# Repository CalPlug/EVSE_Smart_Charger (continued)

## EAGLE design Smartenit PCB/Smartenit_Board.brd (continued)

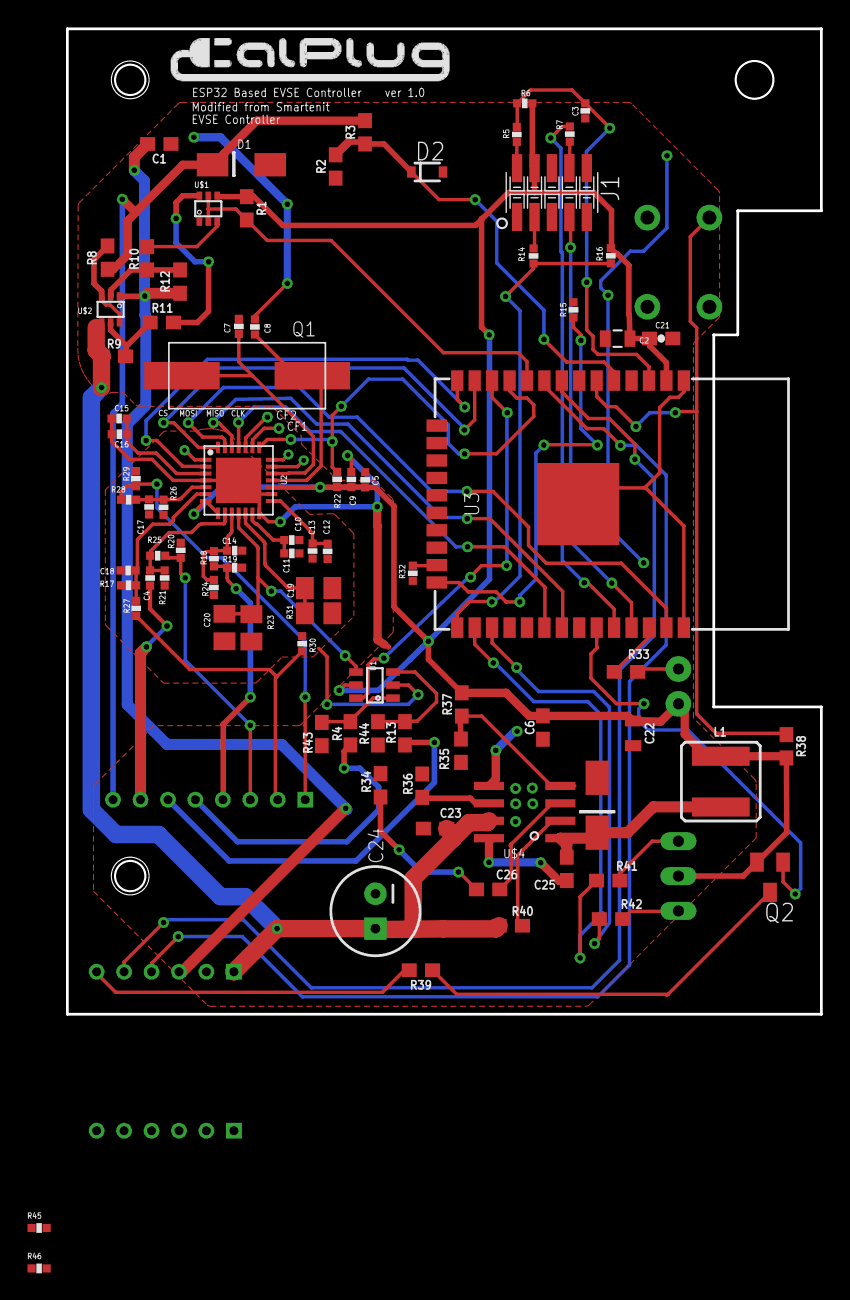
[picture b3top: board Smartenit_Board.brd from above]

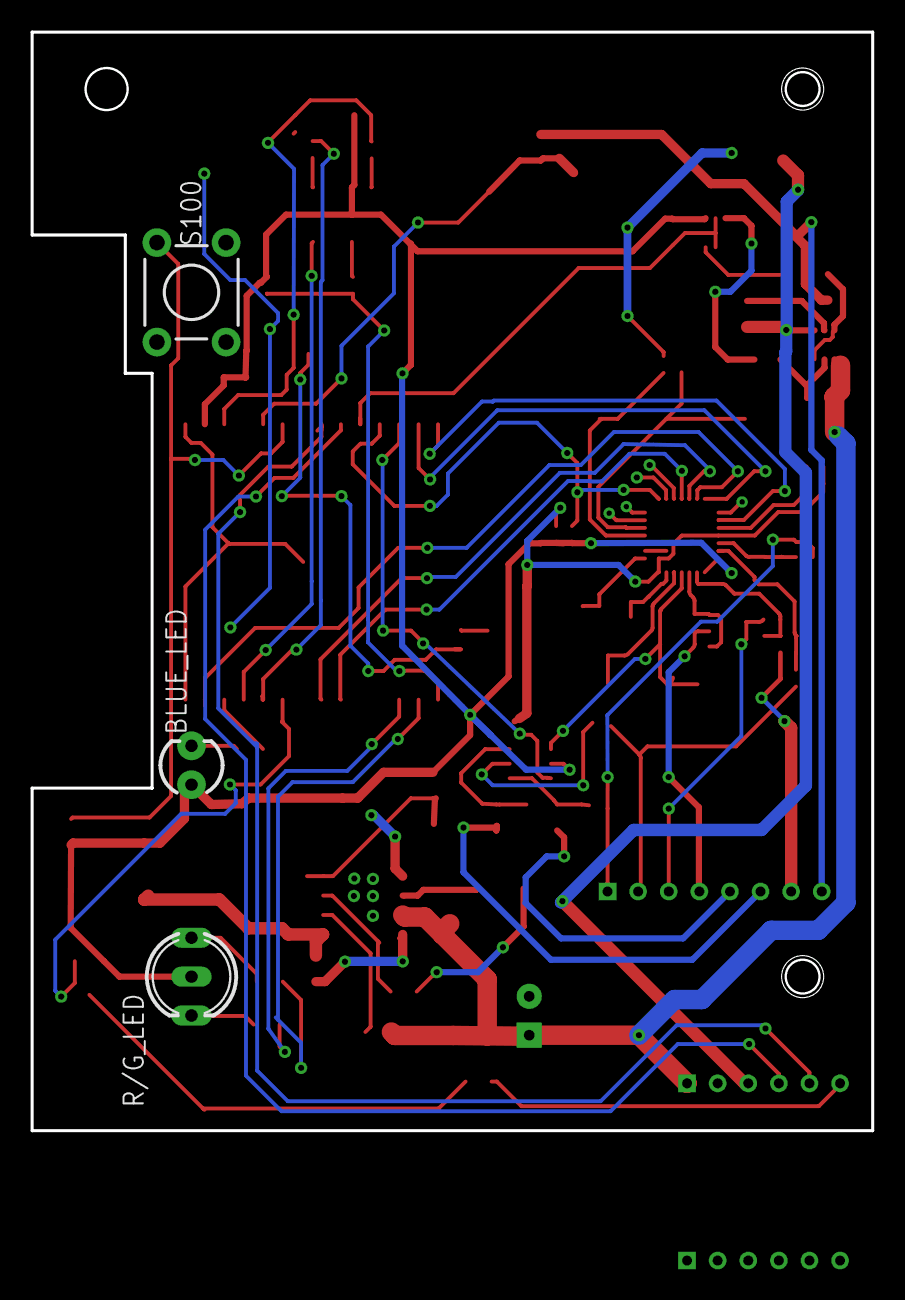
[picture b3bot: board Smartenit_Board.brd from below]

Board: 2 copper layers, 54.9 x 71.8 mm, 91 parts (3 on the bottom side), 69 nets.

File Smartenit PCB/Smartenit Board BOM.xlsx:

Smartenit Board BoM
Qty | Value | Device | Package | Parts | URL | Price per unit | Total quantity (5 boards) | Price (5 boards) | TOTAL
1.0 | 1 uF, 25V | Capacitor | 603.0 | C1 | https://www.mouser.com/ProductDetail/AVX/0603DC105MAT2A?qs=s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 | 0.251 | 10.0 | 2.51
6.0 | 100 nF | Capacitor | 402.0 | C3, C5,C9, C10, C13, C16 | https://www.mouser.com/ProductDetail/Taiyo-Yuden/LMK105BJ104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 | 0.102 | 30.0 | 1.02
3.0 | 100nF | Capacitor | 603.0 | C21,C23, C25 | https://www.mouser.com/ProductDetail/AVX/MM035C104KCZ2A?qs=s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 | 1.51 | 15.0 | 22.65
2.0 | 20 pF | Capacitor | 402.0 | C7, C8 | https://www.mouser.com/ProductDetail/KEMET/CBR04C200F2GAC?qs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 | 0.554 | 10.0 | 5.54
2.0 | 10 uF Polarized | Capacitor | 805.0 | C2, C22 | https://www.mouser.com/ProductDetail/KEMET/T529P106M010AAE20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 | 0.459 | 10.0 | 4.59
4.0 | 33 nF | Capacitor | 402.0 | C4, C14, C17, C18 | https://www.mouser.com/ProductDetail/KEMET/C0402C333K3RACAUT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 | 0.133 | 20.0 | 2.66
2.0 | 33 nF | Capacitor | 805.0 | C19, C20 | https://www.mouser.com/ProductDetail/KEMET/C0805C333G8JACTU?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 | 0.38 | 10.0 | 3.8
1.0 | 22uF/ 6.3V | Capacitor | 603.0 | C6 | https://www.mouser.com/ProductDetail/Murata-Electronics/GRT1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 | 0.36 | 10.0 | 3.6
3.0 | 4.7 uF | Capacitor | 402.0 | C11, C12, C15 | https://www.mouser.com/ProductDetail/AVX/0402ZD475KAT2A?qs=s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 | 0.213 | 15.0 | 3.195
1.0 | 150 pF | Capacitor | 603.0 | C26 | https://www.mouser.com/ProductDetail/KEMET/C0603C151K5RACTU?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 | 0.122 | 10.0 | 1.22
1.0 | 100 uF polarized | Capacitor | PTH | C24 | https://www.mouser.com/ProductDetail/Nichicon/URS1E101MDD?qs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 | 0.195 | 10.0 | 1.95
5.0 | 10K | Resistor | 603.0 | R1, R10, R11, R38,R39 | https://www.mouser.com/ProductDetail/Vishay-BC-Components/MC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 | 0.434 | 25.0 | 10.85
1.0 | 10K | Resistor | 402.0 | R22, | https://www.mouser.com/ProductDetail/Vishay/CRCW040210K0FKED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 | 0.041 | 10.0 | 0.41
1.0 | 56K | Resistor | 603.0 | R2 | https://www.mouser.com/ProductDetail/Panasonic/ERJ-S03J563V?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 | 0.23 | 10.0 | 2.3
1.0 | 200K | Resistor | 603.0 | R3 | https://www.mouser.com/ProductDetail/Panasonic/ERJ-P03F2003V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 | 0.231 | 10.0 | 2.31
3.0 | 1K | Resistor | 603.0 | R4, R8, R13, | https://www.mouser.com/ProductDetail/KOA-Speer/RK73G1JTTD100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 | 0.367 | 15.0 | 5.51
4.0 | 1K | Resistor | 402.0 | R17, R21, R24, R26 | https://www.mouser.com/ProductDetail/KOA-Speer/RK73G1ETTP100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 | 0.367 | 20.0 | 7.34
2.0 | 1K | Resistor | 805.0 | R23, R31 | https://www.mouser.com/ProductDetail/Vishay/RCS08051K00JNEA?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 | 0.19 | 10.0 | 1.9
4.0 | 470.0 | Resistor | 402.0 | R5, R7, R14, R15 | https://www.mouser.com/ProductDetail/Panasonic/ERJ-PA2D4700X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 | 0.2 | 20.0 | 4.0
3.0 | 12K | Resistor | 402.0 | R6, R16, R32 | https://www.mouser.com/ProductDetail/Panasonic/ERA-2AEB123X?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 | 0.585 | 15.0 | 8.78
2.0 | 4.7K | Resistor | 603.0 | R9, R12, | https://www.mouser.com/ProductDetail/KOA-Speer/RK73G1JTTD470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 | 0.367 | 10.0 | 3.67
4.0 | 9.1K | Resistor | 402.0 | R18, R25, R27, R28 | https://www.mouser.com/ProductDetail/Panasonic/ERA-2AEB912X?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 | 0.585 | 20.0 | 11.7
4.0 | 51.0 | Resistor | 402.0 | R19, R20, R29, R30 | https://www.mouser.com/ProductDetail/Panasonic/ERJ-PA2D51R0X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 | 0.2 | 20.0 | 4.0
3.0 | 220.0 | Resistor | 603.0 | R33, R41, R42 | https://www.mouser.com/ProductDetail/Panasonic/ERJ-PB3B2200V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 | 0.161 | 15.0 | 2.42
3.0 | 100K | Resistor | 603.0 | R34, R36, R40 | https://www.mouser.com/ProductDetail/Panasonic/ERJ-PB3B1003V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 | 0.161 | 15.0 | 2.415
1.0 | 40.2K | Resistor | 603.0 | R35 | https://www.mouser.com/ProductDetail/KOA-Speer/RK73H1JTTDD40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 | 0.015 | 10.0 | 0.15
2.0 | 4.7k | Resistor | 603.0 | R43, R44 | https://www.mouser.com/ProductDetail/ROHM-Semiconductor/ESR0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 | 0.103 | 10.0 | 1.03
1.0 | 124K | Resistor | 603.0 | R37 | https://www.mouser.com/ProductDetail/Bourns/CR0603-FX-1243EL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 | 0.033 | 10.0 | 0.33
1.0 | Bicolor LED | R/G Bicoler LED |  | R/G LED | https://www.mouser.com/ProductDetail/Bivar/3BC-3-CA-F?qs=%2f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 | 0.6 | 5.0 | 3.0
1.0 | 8.245018E8 | TVS Diodes |  | D1 | https://www.mouser.com/ProductDetail/Wurth-Electronics/82450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 | 0.28 | 5.0 | 1.4
1.0 | 1n4148 | 1N4148 diode |  | D2 | https://www.mouser.com/ProductDetail/Micro-Commercial-Compon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 | 0.18 | 5.0 | 0.9
1.0 | DTA114YUAT106 | PNP Transistor |  | Q2 | https://www.mouser.com/ProductDetail/ROHM-Semiconductor/DTA1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 | 0.19 | 5.0 | 0.95
1.0 | MP1584 | IC BUCK CONVERTER |  | U$4 | https://www.mouser.com/ProductDetail/Monolithic-Power-System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 | 2.94 | 5.0 | 14.7
1.0 | NA | mini pushbutton switch | NA | S100 | https://www.sparkfun.com/products/97 | 0.35 | 5.0 | 1.75
1.0 | NA | Blue 3mm LED |  | BLUELED | https://www.mouser.com/ProductDetail/Lumex/SSL-LX3054USBD?qs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
1.0 | DMC3400SSDW | MOSFET N/P-CH |  | U$1, U$2 | https://www.digikey.com/product-detail/en/diodes-incorporate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 | 0.51 | 5.0 | 2.55
1.0 | SN74LVC1G3157 | Multiplexer |  | U1 | https://www.digikey.com/product-detail/en/texas-instruments/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 | 0.37 | 5.0 | 1.85
1.0 | ADE7953 | ENERGY METERING |  | U2 | https://www.digikey.com/product-detail/en/analog-devices-inc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 | 4.16 | 5.0 | 20.8
1.0 | ESP32 WROOM-02 | ESP32WROOM-02 |  | U3 | https://www.digikey.com/products/en?mpart=3320&v=1528 | 8.95 | 5.0 | 44.75
1.0 | MP1584 | IC BUCK CONVERTER |  | U$4 | https://www.digikey.com/product-detail/en/monolithic-power-s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 | 2.15 | 5.0 | 10.75
1.0 | 8 pin 2mm connector | 8 pin 2mm connector |  | U$3 | https://www.digikey.com/product-detail/en/molex-llc/08940008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 | 0.48 | 5.0 | 2.4
1.0 | 2mm connector 6 pins | 2mm connector 6-pins |  | U$5 | https://www.digikey.com/product-detail/en/molex-llc/08940006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 | 0.3 | 5.0 | 1.5
1.0 | B340A-13-F | schottky diode |  | D3 | https://www.digikey.com/product-detail/en/diodes-incorporate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 | 0.46 | 5.0 | 2.3
1.0 | Oscillator | 3.57MHz oscillator |  | Q1 | https://www.digikey.com/product-detail/en/txc-corporation/9C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 | 0.36 | 5.0 | 1.8
1.0 | 10-Pin Header | 10-Pin Header |  | J1 | https://www.digikey.com/product-detail/en/amphenol-fci/20021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 | 0.45 | 5.0 | 2.25 | 235.5

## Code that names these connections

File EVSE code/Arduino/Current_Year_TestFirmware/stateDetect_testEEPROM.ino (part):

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#include <EEPROM.h>
#include <esp32-hal-gpio.h>

const int relay1 = 32;
const int relay2 = 33;
const int relayenable = 21; // output
//NONLINEAR REGRESSION VALUE
double StateAThresholdLookupBase = 7.7303; 
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int ADC_C = 1414; //3480; // ADC value when plugged and charging (center point)
int ADC_Cthreshold = 1300; // ADC threshold value when plugged and charging (variance threshold)Plus and minus

int ADC_E = 10; // State E - Error with the pilot grounded
int ADC_Ethreshold = 10; // (variance threshold) Plus and minus

//State D does not exist for LiPo batteries that are charged without venting

int ADC_F = 10; // State F - Error with the pilot Low set at -12V constant, this is an unknown/error condition
int ADC_Fthreshold = 10; // \(variance threshold) Plus and minus


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int relayEnable = 0;
int pilotfreq = 1000;
int resolution = 10; // for LED PWM
int pilotresolution = 13; // for Pilot PWM, be careful range is modified. Changing this value will not propogate everything required. Must update both intermediate value range AND mapping

// variables to keep track of the data line on ADC
int average = 0;
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  pinMode(relayenable, OUTPUT);
  digitalWrite(relayenable, HIGH);
  digitalWrite(relayenable, LOW); // when this is low, the enable pin is valid  
  pinMode(relay1, OUTPUT);
  digitalWrite(relay1, LOW);
  pinMode(relay2, OUTPUT);
  digitalWrite(relay2, LOW);
  delay(1000);
  digitalWrite(relayenable, HIGH); // turn off relay enable pin
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
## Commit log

2017-12-18 Project Directory Update
2017-12-24 Project Profile
2017-12-24 Create EV_Simulator
2017-12-29 added EVSE Sim
2017-12-29 FPGA Design
2017-12-30 EVSE Abstract Design
    EVSE Smart Charger Abstract Electronics Design and Connections
2017-12-30 NXP Board update
    Updated airwires and silkscreen collisions
2018-01-08 Added Arduino EVSE Code
2018-01-10 -support for dip switch added
    The light bulb can now be modified into several states by a dip switch.
    Modified the different modes for each state to reflect requests.
2018-01-10 relay test
2018-01-10 removed io expander
2018-01-11 NXP fixes
2018-01-16 -adjusted gain
    added debug options
2018-01-16 -adjusted gain values
2018-01-16 -adjusted values
2018-01-17 okjoinijn
2018-01-17 -created copies of arduino code
    Made copies, added new folder, adjusted simulator
2018-01-21 added flash memory
2018-01-22 added file copies
2018-01-22 code alterations
2018-01-23 added C conversions
    - conversions for Pilot.h and Pilot.c are added. Need to adjust pin class
2018-01-23 regerhethre
2018-01-24 dgsdg
2018-01-24 avr libs
2018-01-24 added wprogram.h
2018-01-24 set_state
2018-01-24 -Added functions
2018-01-25 set_relay
2018-01-25 tested
2018-01-26 added FCB stuff
2018-01-29 uploaded new FPGA design folders
2018-01-30 modified constraints
2018-01-30 -added header/cleaned functions
2018-01-30 -added ESP8266 keywords
2018-01-31 -made adjustments/added wattmeter
2018-01-31 some changes to levelDetection
2018-01-31 changes to leveldetection
2018-01-31 getgpiopin
2018-01-31 -adjustments
2018-01-31 -level detection gpio reads
2018-01-31 added software/firmware files
2018-01-31 -added Readwattmeter function
2018-01-31 - added interupts
2018-01-31 esp8266 stuff
2018-02-12 -added nxp main
2018-02-14 -added new functions
2018-02-14 -added GFI test
2018-02-14 DC relays on or off
2018-02-14 -state switching
2018-02-16 added smartenit eagle file
2018-02-18 additions to smartenit schematic
2018-02-18 tested GFI, connects online
2018-02-18 -added MQTT functionality
2018-02-19 MQTT functionality added
    Can modify the rate of the care using special MQTT messages. Can additionally adjust the state of the car.
2018-02-19 -added additional MQTT functions
    Device can now respond to certain requests and publish messages
2018-02-21 CHS and LED
    added check state and led state depending on state.
2018-02-21 dimensions changed
    Design changes to base board dimensions
2018-02-21 updated layout
    dimension changes and re-arranging components
2018-02-21 Component Rearrangement
    Rearranged components on board to fit
2018-02-22 New dimensions
    fixed hole spacing and reorganized based on new design
2018-02-22 New dimensnions and lights adjusted
    moved lights to correct position
2018-02-23 button as interrupt
2018-02-23 connecttowifi problems
    implemented 3 led's but couldnt test because it would not upload for some reason smh
2018-02-23 Update dimsension
    updated dimensions and spacing for layout
2018-02-23 -added LED PWM support
2018-02-23 new topics
2018-02-23 -minor adjustments
2018-02-24 Updated schematic dimensions
    dimensions and interspacing between holes LEDs and pin headers
2018-02-24 changed 2mm headers
2018-02-24 new positions and dimensions
    updated new part positions and new dimensions for holes and headers
2018-02-24 new update
    moved resistor
2018-02-24 sgsdg
2018-02-24 Revert "new update"
    This reverts commit 66083c590e8f695bb00e8bd9e9dbc0c4c991c1d6.
2018-02-24 Revert "new positions and dimensions"
    This reverts commit 1058d715852c857a229c7a035a971a2650f9524b.
2018-02-24 revert attempt 3
2018-02-24 poooop
2018-02-24 Revert "Updated schematic dimensions"
    This reverts commit 3cdf2f2f25e8d79ca338aabb6b6922afd7b4b7ff.
2018-02-24 Revert "changed 2mm headers"
    This reverts commit 813b977e52fbc36cb1bd6f6e005be8e5b7ce1752.
2018-02-24 new no error
2018-02-24 headers
2018-02-24 no error still
2018-02-24 no error
2018-02-24 revert
2018-02-24 update (google drive supported now)
2018-02-25 -lights can now blink
    blinking lights denote state
2018-02-25 -added button interrupts, fixed bug
    Device can now check number of times button is pressed during five second interval. Fixed bug where program was not uploaded to device
2018-02-26 -added button functionality
    Buttons can now cause different effects on the charger state, including shutting down loads, and reseting the device
2018-02-26 routed board
    routed and added pin connections to ESp module
2018-02-26 moved two caps
    proximity issue reslved with caps by crystal.
2018-02-26 -added topics
2018-02-26 blah
2018-02-26 smartenit load device/reset
2018-02-26 push
2018-02-26 changed blue LED
2018-02-26 Finished Routing
    Finished aligning dimensions, routing, fixing trace sizes and fixed cap on 12V line.
2018-02-26 renumber board
2018-02-26 Fixed Silk Screen
    Fixed numbering of components and silk screen
2018-02-27 reset parameters
2018-02-27 reset params (reset all)
2018-02-27 -mqtt message functionality
2018-02-27 Fixed Silk Screen final before sending to Al
    fixed silk screen and renumbered parts
2018-02-28 Changed ground planes
    separated into analog and digital grounds. Rearachnged layout for better coupling.
2018-02-28 minor changes to ground planes
2018-02-28 fixed diodes
2018-02-28 New Revision with grounds connected
2018-03-01 fixed right angles, ground planes, connectors
2018-03-01 Made Al's Revision Suggestions
    -no right angles
    -flipped header
    -New digital ground plane (redid ground signals)
    -Reorganized ADE7953 components
2018-03-01 Additional Modifications from Al
    -moved mplex to connector region
    -fixed ground connections to match Als exactly
    -additional reogranization of traces
2018-03-01 updated again
2018-03-01 hole size updated
2018-03-02 -more MQTT functions and LED updates
2018-03-07 - added Pilot Read/ Pilot output
    Device can read ADC values from input pin to determine current state. Will modify the board's state automatically to reflect the input voltage. Can also generate a pilot output signal for the car to 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
2018-03-14 resets done
2018-03-16 Added functions
2018-03-19 Rerouting for new pins
2018-03-24 -merged Shermaine's Wifi protocols
    Implemented full message check for MQTT, adjusted subscriptions for MQTT, adjusted values for pilot output
2018-03-25 -Added Wattmeter libraries for ESP32
2018-03-26 fixed MPLEX package, reverses L1/L2 lines
2018-03-27 updated #1
2018-03-27 updated #2
2018-03-27 updates #3
2018-03-27 update #4
2018-03-27 fixed more bugs, removed personal information
2018-03-27 -fixed ranges for ADC
2018-03-27 -merged AP mode with Brandytest. Still a little buggy
2018-03-27 -added immediate Wifi setup after AP
2018-03-27 -fixed spacing
2018-03-28 jhiuh
2018-03-28 -added GFI, removed personal info, pilot readings are from actual car
2018-03-29 -added additional libraries, entered Mike's AP into brandytest
2018-03-29 Update current channel calibrations
2018-03-29 stuff
2018-03-30 -added EEPROM functionality, added Brandon's formulas, added initiliazation script
2018-03-30 Added CF1 and CF2 test points
    Last edit for board design for smartenit
2018-03-30 last edits
2018-03-30 cf1 AND cf2
2018-03-30 Last edits
    Added grounds for new resistors and added test points for REVP, ZX, and ZX_I
2018-04-02 updated cap sizes
2018-04-03 PowerBoard
2018-04-10 -updates
2018-04-12 -adjusted MQTT parameters
2018-04-12 -tests for AP mode
2018-04-17 -fixed EEPROM reset, adjusted AP mode
2018-04-19 -fixed button bug
2018-04-19 -changed SSID of AP, light bug fix
2018-04-19 -adjustments to AP
2018-04-24 -fixed AP special characters
2018-05-03 added JP2 header
2018-05-03 added notes
2018-05-03 added dot for programming header
2018-05-03 fixed labeling and other stuff
2018-05-07 -adjusted report
2018-05-16 changes to brandy_testeeprom and pull down
    changed pull down on button to 4.7.
2018-05-22 Organized directories
2018-05-22 general bug fixes
2018-05-24 Added README for EEPROM script
2018-05-25 -disabled tests for debugging
2018-05-30 Project Poster
2018-05-30 Update Matlab GUI Code
2018-05-30 Update with latest Matlab GUI for Serial connection to charger
2018-05-31 Updated BOM
2018-05-31 Added comments
2018-06-01 Comments added
2018-06-01 General fixes
2018-06-01 Update Calculations
2018-06-01 Update Comments
2018-06-01 added libraries
2018-07-02 Update Processing Code
2018-07-03 Added most recent EVSE control file
2019-05-31 Upload of 18-19 EVSE firmware
